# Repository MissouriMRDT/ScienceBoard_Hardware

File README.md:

# ScienceBoard-Hardware
Raman spectrometer and science box sensor

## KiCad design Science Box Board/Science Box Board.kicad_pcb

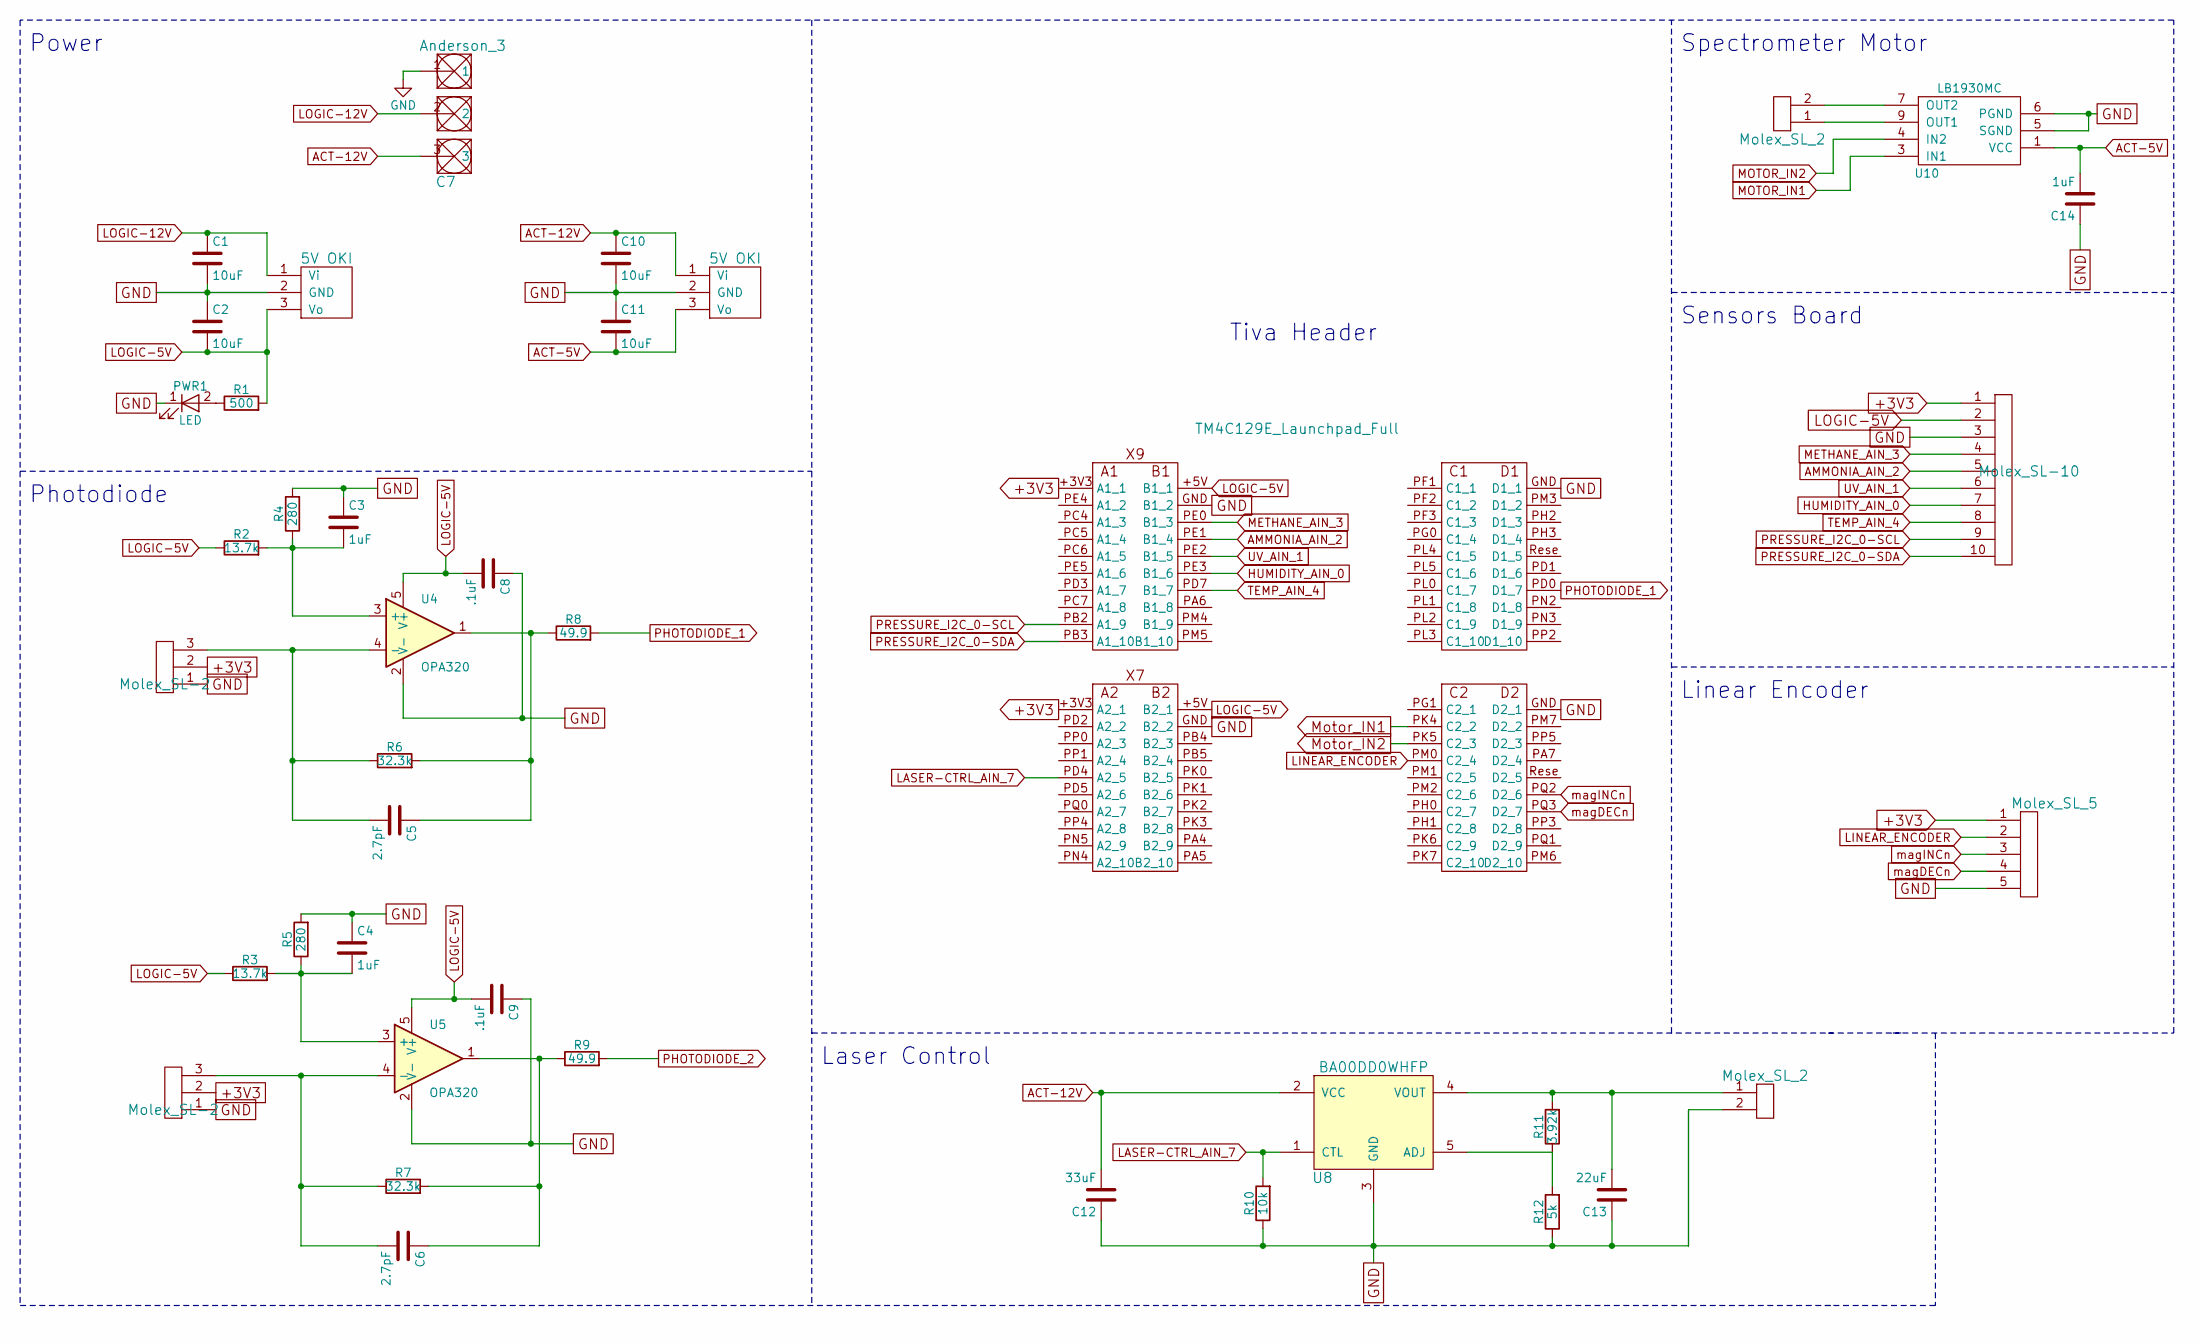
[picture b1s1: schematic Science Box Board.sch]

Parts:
C1, C2, C10, C11: 10uF; C_0603_HandSoldering
C3, C4, C14: 1uF; C_0603_HandSoldering
C5, C6: 2.7pF; C_0603_HandSoldering
C7: Anderson_3; Anderson_3_Horisontal_Side_by_Side
C8, C9: .1uF; C_0603_HandSoldering
C12: 33uF; C_0603_HandSoldering
C13: 22uF; C_0603_HandSoldering
PWR1: LED; LED_1206_HandSoldering
R1: 500; R_0603_HandSoldering
R2, R3: 13.7k; R_0603_HandSoldering
R4, R5: 280; R_0603_HandSoldering
R6, R7: 32.3k; R_0603_HandSoldering
R8, R9: 49.9; R_0603_HandSoldering
R10: 10k; R_0603_HandSoldering
R11: 3.92k; R_0603_HandSoldering
R12: 5k; R_0603_HandSoldering
U1, U2: Molex_SL-2; MOLEX_SL_2_Horizontal
U3, U6: 5V OKI; OKI_Horisontal
U4, U5: OPA320; SOT-23-5_HandSoldering
U7: TM4C129E_Launchpad_Full; TM4C129E_Launchpad_FULL_Booster
U8: BA00DD0WHFP; TO-252-5_TabPin3
U9, U12: Molex_SL_2; MOLEX_SL_2_Horizontal
U10: LB1930MC; SOIC_10NB_2
U11: Molex_SL-10; MOLEX_SL_10_Horizontal
U13: Molex_SL_5; MOLEX_SL_5_Horizontal

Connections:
+3V3: U1.2, U2.2, U7.+3V3 (A1_1), U11.1, U13.1
ACT-5V: C11.2, C14.2, U6.3 (Vo), U10.1 (VCC)
ACT-12V: C7.3, C10.1, C12.2, U6.1 (Vi), U8.2 (VCC)
AMMONIA_AIN_2: U7.PE1 (B1_4), U11.5
GND: C1.2, C2.1, C3.1, C4.1, C7.1, C8.1, C9.1, C10.2, C11.1, C12.1, C13.1, C14.1, PWR1.1 (K), R4.2, R5.2, R10.1, R12.1, U1.1, U2.1, U3.2 (GND), U4.2 (V-), U5.2 (V-), U6.2 (GND), U7.GND (B1_2), U8.3 (GND), U10.5 (SGND), U10.6 (PGND), U11.3, U12.2, U13.5
HUMIDITY_AIN_0: U7.PE3 (B1_6), U11.7
LASER-CTRL_AIN_7: R10.2, U7.PD4 (A2_5), U8.1 (CTL)
LINEAR_ENCODER: U7.PM0 (C2_4), U13.2
LOGIC-5V: C2.2, C8.2, C9.2, R1.2, R2.1, R3.1, U3.3 (Vo), U4.5 (V+), U5.5 (V+), U7.+5V (B1_1), U11.2
LOGIC-12V: C1.1, C7.2, U3.1 (Vi)
METHANE_AIN_3: U7.PE0 (B1_3), U11.4
MOTOR_IN1: U7.PK4 (C2_2), U10.3 (IN1)
MOTOR_IN2: U7.PK5 (C2_3), U10.4 (IN2)
unnamed: C3.2, R2.2, R4.1, U4.3 (+)
unnamed: C4.2, R3.2, R5.1, U5.3 (+)
unnamed: C5.1, R6.2, R8.1, U4.1
unnamed: C5.2, R6.1, U1.3, U4.4 (-)
unnamed: C6.1, R7.2, R9.1, U5.1
unnamed: C6.2, R7.1, U2.3, U5.4 (-)
unnamed: C13.2, R11.2, U8.4 (VOUT), U12.1
unnamed: PWR1.2 (A), R1.1
unnamed: R11.1, R12.2, U8.5 (ADJ)
unnamed: U9.2, U10.7 (OUT2)
unnamed: U9.1, U10.9 (OUT1)
PHOTODIODE_1: R8.2, U7.PD0 (D1_7)
PRESSURE_I2C_0-SCL: U7.PB2 (A1_9), U11.9
PRESSURE_I2C_0-SDA: U7.PB3 (A1_10), U11.10
TEMP_AIN_4: U7.PD7 (B1_7), U11.8
UV_AIN_1: U7.PE2 (B1_5), U11.6
magDECn: U7.PQ3 (D2_7), U13.4
magINCn: U7.PQ2 (D2_6), U13.3

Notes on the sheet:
Laser Control
Sensors Board
Photodiode
Tiva Header
Linear Encoder
Power
Spectrometer Motor

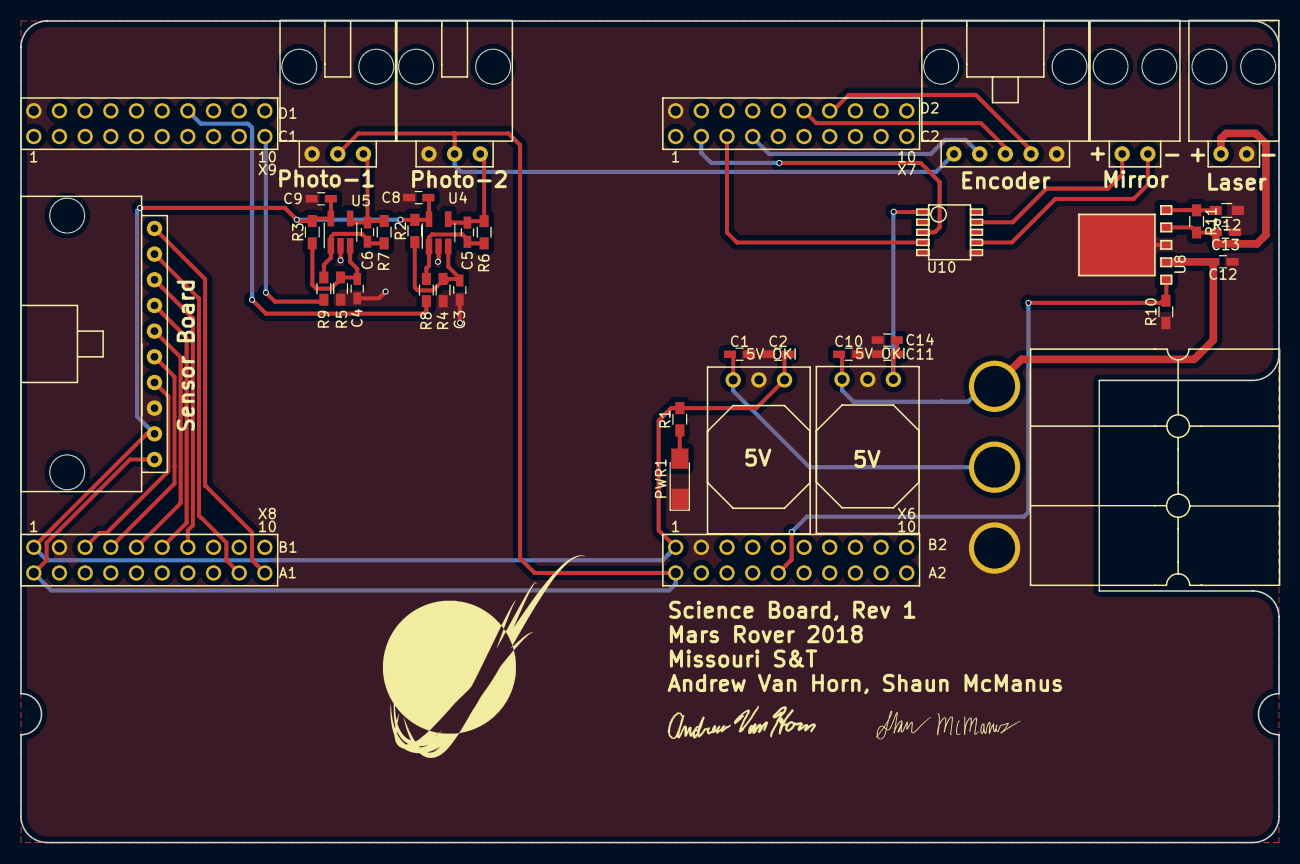
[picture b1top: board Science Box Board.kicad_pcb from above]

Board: 2 copper layers, 124.5 x 81.3 mm, 40 parts (0 on the bottom side), 31 nets.

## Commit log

2018-03-12 Created Photodiode Schematic and preliminary board.
    Awaiting board dimensions and mounting requirements.
2018-03-13 Upload of partially completed signals booster. Current revision contains tiva headers and connections for the photodiodes, sensors board, laser control, and linear encoder
2018-03-13 Adjusted directory structure to keep kicad files in one folder
2018-03-20 Added power and filtering section for andersons, oki, etc.
2018-03-21 Added notes from meeting about changes needed for signals board schematic
2018-03-21 Added Power section with Oki and Anderson connections
2018-03-21 Added photodiodes circuitry and connectors
2018-03-22 Added Laster Control
2018-03-23 Created Photodiode board
2018-03-24 Added Spectrometer motor, notes about tiva pin mappings needed. Created device / package associations and generated netlist
2018-03-24 Added a few additional notes in the schematic for clarity
2018-03-26 Finalised schematic and began working on board layout
2018-03-26 Finished Board
2018-03-27 Finalized board and generated gerbs
    Changed name of board from "Science Signals Booster" to "Science Box Board". Board Review for Rev 1, generated Gerbs
2018-03-28 Generated Final Gerbs
2018-04-19 Modified footprint of LD
2018-04-20 Modified board layout
2018-04-20 Changed Molex SL 2 to SL 3 for photodiodes and added +3v3 to connection
2018-04-20 Changed Molex SL2 to SL3 for photodiode connections and added 3v3 to them
2018-04-22 Added new Ba00dwop footrpint and switched SL2 to SL3 for Photodiode
